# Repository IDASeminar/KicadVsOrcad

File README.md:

# KicadVsOrcad

Med frigivelsen er Kicad blevet endnu stærkere og er nu fuldt ud dækkende til mange prof udlægnings opgaver. Der er stadig ting, som gøres bedre i andre programmer, især når det gælder highspeed, som DDR hukommelse. Men til rigtig mange industrielle opgaver er KiCad fuldt ud nok til at du kan gennemfører din opgave. Da det samtidigt er gratis og uden nogle begrænsninger, kan man jo kun blive glad for open source.
Agenda:
* Gennemgang af Kicad
* Demoprojekt
* "Bring your project". Få hjælp til at starte dit project.
* Panelizing og smd assembly
* BOM

Fordragsholder er Gert Lauritsen, der har arbejdet som udviklingsingeniør i mange år indenfor forskning og industri. Dette har været både på hardware og software.

[Video](https://youtu.be/Q6-I2eaVBcE)

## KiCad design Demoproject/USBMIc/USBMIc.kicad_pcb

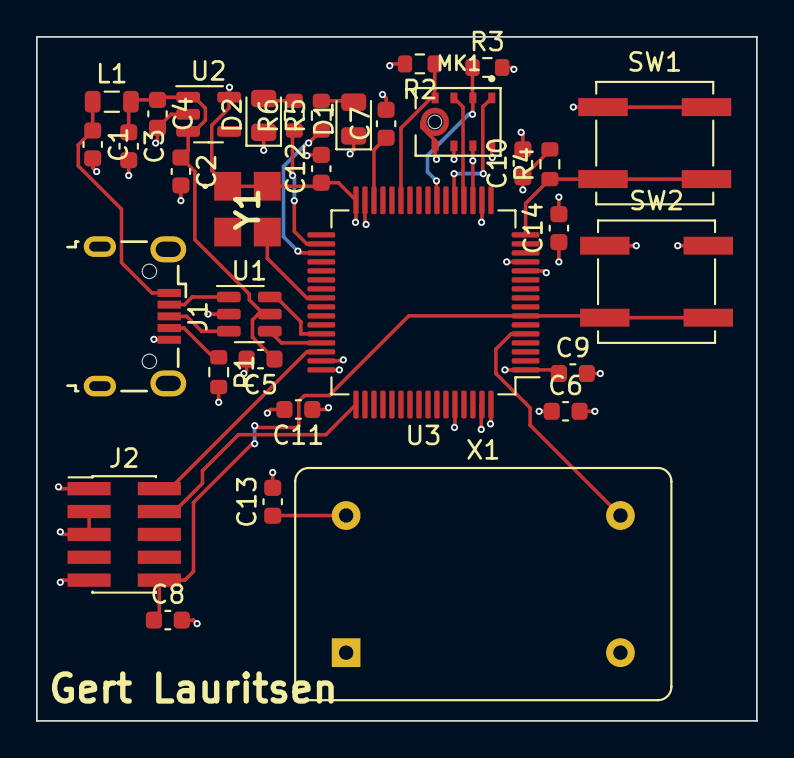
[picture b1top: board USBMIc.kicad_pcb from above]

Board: 4 copper layers, 40.0 x 38.0 mm, 33 parts (0 on the bottom side), 24 nets.

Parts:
C1: 10nF; C_0603_1608Metric
C2, C8: 100nF; C_0603_1608Metric
C3, C7: 4u7; C_0603_1608Metric
C4: 22uf; C_0603_1608Metric
C5, C6, C9, C10, C11, C12, C13, C14: 1uF; C_0603_1608Metric
D1, D2: LED; LED_0805_2012Metric
J1: USB_B_Micro; USB_Micro-B_Wuerth_629105150521
J2: Prog; PinHeader_2x05_P1.27mm_Vertical_SMD
L1: INDUCTOR; L_0805_2012Metric
MK1: INMP441ACEZ-R7; MIC_INMP441ACEZ-R7
R1, R2, R3, R4: 100k; R_0603_1608Metric
R5, R6: 330; R_0603_1608Metric
SW1, SW2: SW_Push; SW_SPST_B3SL-1002P
U1: USBLC6-2SC6; SOT-23-6
U2: LP5907MFX-3.3; SOT-23-5
U3: STM32F446RCTx; LQFP-64_10x10mm_P0.5mm
X1: ACO-xxxMHz; Oscillator_DIP-14
Y1: SG-8018CB_12.2880M-TJHPA3; SG8018CB122880MTJHPA3

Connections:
+3V3: C6.1, C9.1, C10.1, C11.1, C12.1, C13.1, C14.1, J2.1, MK1.7 (VDD), MK1.8 (CHIPEN), R4.2, U2.5 (OUT), U3.1 (VBAT), U3.13 (VDDA), U3.19 (VDD), U3.32 (VDD), U3.48 (VDD), U3.64 (VDD), X1.14 (Vcc), Y1.1 (OE), Y1.4 (VCC)
+5V: C2.1, C3.1, C4.1, C5.1, L1.2, U1.5 (VBUS), U2.1 (IN), U2.3 (EN)
CK: MK1.1 (SCK), U3.21 (PA5)
GND: C1.2, C2.2, C3.2, C4.2, C5.2, C6.2, C7.2, C8.2, C9.2, C10.2, C11.2, C12.2, C13.2, C14.2, D1.1 (K), D2.1 (K), J1.5 (GND), J1.6 (Shield), J2.3, J2.5, J2.9, MK1.5 (GND), MK1.6 (GND), MK1.9 (GND), R1.2, R2.2, R3.2, SW1.1, SW2.1, U1.2 (GND), U2.2 (GND), U3.12 (VSSA), U3.18 (VSS), U3.31 (VSS), U3.47 (VSS), U3.60 (BOOT0), U3.63 (VSS), X1.7 (GND)
LR: MK1.4 (L/R), R2.1, U3.27 (PB1)
Mute: R4.1, SW1.2, U3.16 (PA2)
unnamed: C1.1, J1.1 (VBUS), L1.1
unnamed: C7.1, U3.30 (VCAP_1)
unnamed: D1.2 (A), R5.2
unnamed: D2.2 (A), R6.2
unnamed: J1.2 (D-), U1.1 (I/O1)
unnamed: J1.3 (D+), U1.3 (I/O2)
unnamed: J1.4 (ID), R1.1
unnamed: R5.1, U3.35 (PB14)
unnamed: R6.1, U3.34 (PB13)
unnamed: U3.5 (PH0), X1.8 (OUT)
unnamed: U3.40 (PC9), Y1.3 (OUT)
RST: C8.1, J2.10, SW2.2, U3.7 (NRST)
SD: MK1.2 (SD), R3.1, U3.23 (PA7)
SWCLK: J2.4, U3.49 (PA14)
SWDIO: J2.2, U3.46 (PA13)
USB_N: U1.6 (I/O1), U3.44 (PA11)
USB_P: U1.4 (I/O2), U3.45 (PA12)
WS: MK1.3 (WS), U3.20 (PA4)

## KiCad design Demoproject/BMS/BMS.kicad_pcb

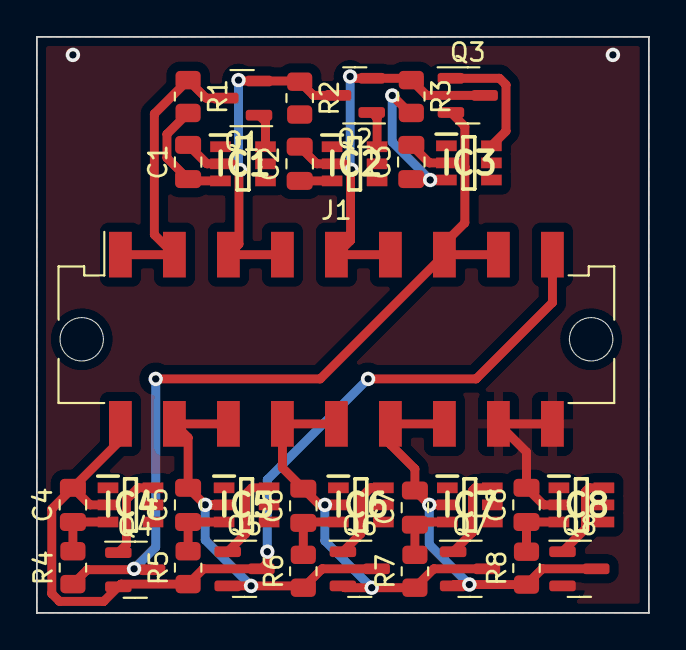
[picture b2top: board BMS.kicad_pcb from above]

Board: 2 copper layers, 34.0 x 32.0 mm, 33 parts (0 on the bottom side), 25 nets.

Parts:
C1, C2, C3, C4, C5, C6, C7, C8: 100nF; C_0805_2012Metric
IC1, IC2, IC3, IC4, IC5, IC6, IC7, IC8: HY2213-BB3A; SOT95P280X140-6N
J1: Conn_02x09_Odd_Even; Molex_Micro-Fit_3.0_43045-1815_2x09_P3.00mm_Vertical
Q1, Q2, Q3, Q4, Q5, Q6, Q7, Q8: AO3400A; SOT-23
R1, R2, R3, R4, R5, R6, R7, R8: 100R; R_0805_2012Metric

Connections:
B0: J1.1, J1.2, Q1.3 (D), R1.1
B1: C1.2, IC1.2 (VDD), J1.3, J1.4, Q1.2 (S), Q2.3 (D), R2.1
B2: C2.2, IC2.2 (VDD), J1.5, J1.6, Q2.2 (S), Q3.3 (D), R3.1
B3: C3.2, IC3.2 (VDD), J1.7, J1.8, Q3.2 (S), Q4.3 (D), R4.1
B4: C4.2, IC4.2 (VDD), J1.9, J1.10, Q4.2 (S), Q5.3 (D), R5.1
B5: C5.2, IC5.2 (VDD), J1.11, J1.12, Q5.2 (S), Q6.3 (D), R6.1
B6: C6.2, IC6.2 (VDD), J1.13, J1.14, Q6.2 (S), Q7.3 (D), R7.1
B7: C7.2, IC7.2 (VDD), J1.15, J1.16, Q7.2 (S), Q8.3 (D), R8.1
GND: C8.2, IC8.2 (VDD), J1.17, J1.18, Q8.2 (S)
unnamed: C1.1, IC1.3 (VSS), R1.2
unnamed: C2.1, IC2.3 (VSS), R2.2
unnamed: C3.1, IC3.3 (VSS), R3.2
unnamed: C4.1, IC4.3 (VSS), R4.2
unnamed: C5.1, IC5.3 (VSS), R5.2
unnamed: C6.1, IC6.3 (VSS), R6.2
unnamed: C7.1, IC7.3 (VSS), R7.2
unnamed: C8.1, IC8.3 (VSS), R8.2
unnamed: IC1.6 (OUT), Q1.1 (G)
unnamed: IC2.6 (OUT), Q2.1 (G)
unnamed: IC3.6 (OUT), Q3.1 (G)
unnamed: IC4.6 (OUT), Q4.1 (G)
unnamed: IC5.6 (OUT), Q5.1 (G)
unnamed: IC6.6 (OUT), Q6.1 (G)
unnamed: IC7.6 (OUT), Q7.1 (G)
unnamed: IC8.6 (OUT), Q8.1 (G)

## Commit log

2022-03-08 powerpoint oplæg
2022-03-08 read update
2022-03-28 opgave 1
2022-03-28 powerpoint update
2022-03-30 pcb layout
2022-03-30 power point update
2022-04-01 video added
2022-04-01 oprydning
